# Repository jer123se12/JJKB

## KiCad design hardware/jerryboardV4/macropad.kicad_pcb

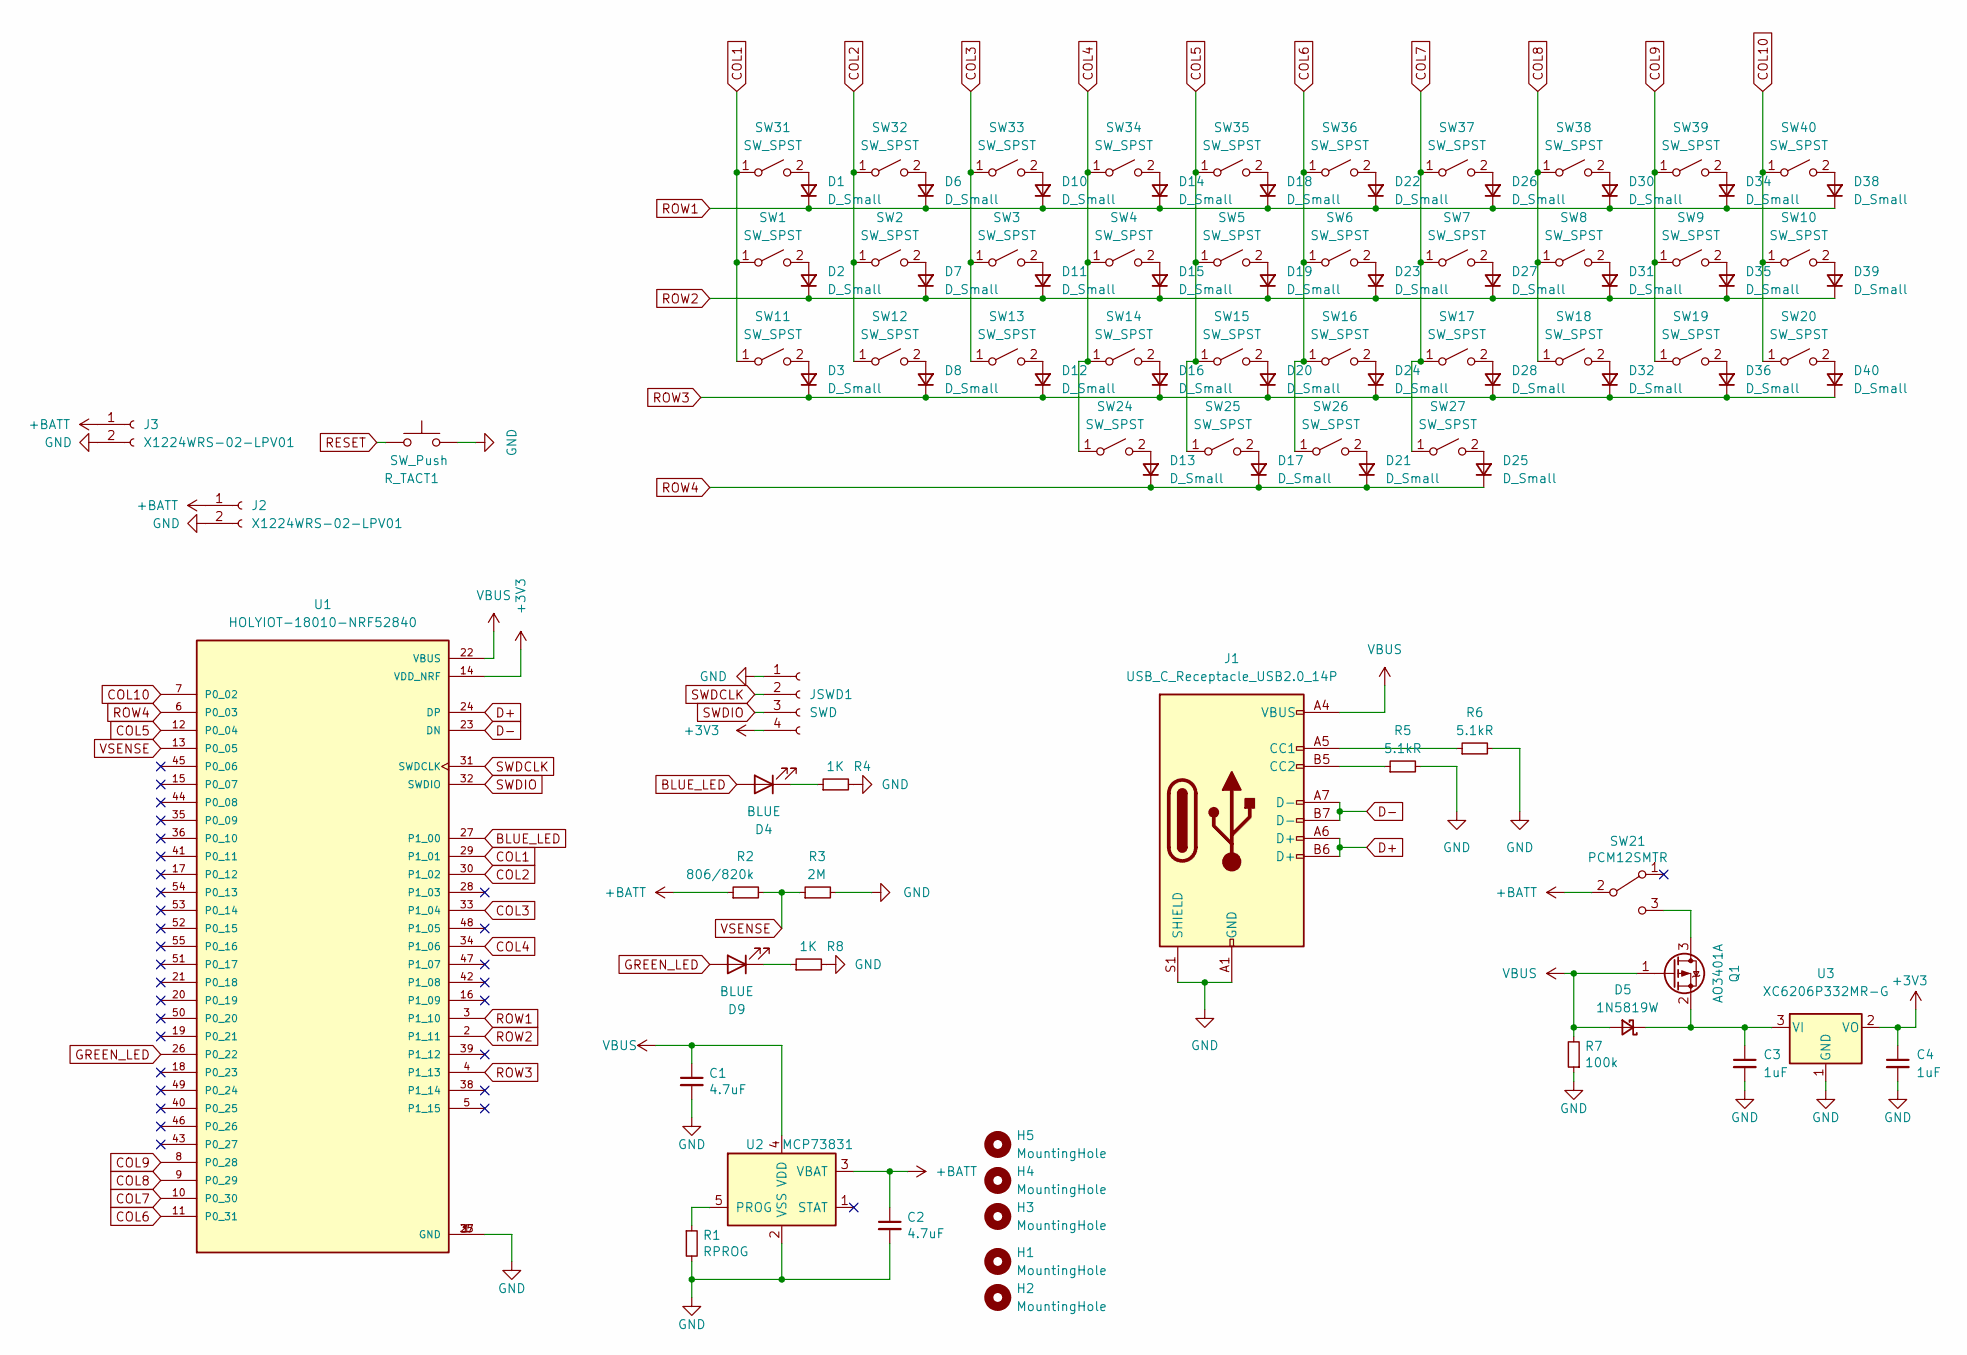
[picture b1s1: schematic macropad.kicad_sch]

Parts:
C1, C2: 4.7uF; C_0603_1608Metric; LCSC C19666
C3, C4: 1uF; C_0603_1608Metric; LCSC C1592
D1, D2, D3, D6, D7, D8, D10, D11, D12, D13, D14, D15, D16, D17, D18, D19, D20, D21, D22, D23, D24, D25, D26, D27, D28, D30, D31, D32, D34, D35, D36, D38, D39, D40: D_Small; D_SOD-123
D4, D9: BLUE; LED_0603_1608Metric; LCSC C72041
D5: 1N5819W; D_SOD-123; LCSC C169540
H1, H2, H3, H4, H5: MountingHole; MountingHole_5.3mm_M5
J1: USB_C_Receptacle_USB2.0_14P; USB_C_Receptacle_HRO_TYPE-C-31-M-12
J2: X1224WRS-02-LPV01; PinHeader_1x02_P2.54mm_Vertical; LCSC C528028
J3: X1224WRS-02-LPV01; Molex_Pico-EZmate_78171-0002_1x02-1MP_P1.20mm_Vertical; LCSC C528028
JSWD1: SWD; PinHeader_1x04_P2.54mm_Vertical
Q1: AO3401A; SOT-23; LCSC C15127
R1: RPROG; R_0603_1608Metric; LCSC C22978
R2: 806/820k; R_0603_1608Metric; LCSC C103828
R3: 2M; R_0603_1608Metric; LCSC C22976
R4, R8: 1K; R_0603_1608Metric; LCSC C21190
R5, R6: 5.1kR; R_0603_1608Metric
R7: 100k; R_0603_1608Metric; LCSC C25803
R_TACT1: SW_Push; Panasonic_EVQPUL_EVQPUC; LCSC C79175
SW1, SW2, SW3, SW4, SW5, SW6, SW7, SW8, SW9, SW10, SW11, SW12, SW13, SW14, SW15, SW16, SW17, SW18, SW19, SW20, SW24, SW25, SW26, SW27, SW31, SW32, SW33, SW34, SW35, SW36, SW37, SW38, SW39, SW40: SW_SPST; SW_Kailh_Choc_V1
SW21: PCM12SMTR; SW_SPDT_PCM12; LCSC C221841
U1: HOLYIOT-18010-NRF52840; XCVR_HOLYIOT-18010-NRF52840
U2: MCP73831; SOT-23-5; LCSC C14879
U3: XC6206P332MR-G; SOT-23; LCSC C5446

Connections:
+3V3: C4.1, JSWD1.4, U1.14 (VDD_NRF), U3.2 (VO)
+BATT: C2.1, J2.1, J3.1, R2.1, SW21.2 (B), U2.3 (VBAT)
BLUE_LED: D4.2 (A), U1.27 (P1_00)
COL1: SW1.1 (A), SW11.1 (A), SW31.1 (A), U1.29 (P1_01)
COL2: SW2.1 (A), SW12.1 (A), SW32.1 (A), U1.30 (P1_02)
COL3: SW3.1 (A), SW13.1 (A), SW33.1 (A), U1.33 (P1_04)
COL4: SW4.1 (A), SW14.1 (A), SW24.1 (A), SW34.1 (A), U1.34 (P1_06)
COL5: SW5.1 (A), SW15.1 (A), SW25.1 (A), SW35.1 (A), U1.12 (P0_04)
COL6: SW6.1 (A), SW16.1 (A), SW26.1 (A), SW36.1 (A), U1.11 (P0_31)
COL7: SW7.1 (A), SW17.1 (A), SW27.1 (A), SW37.1 (A), U1.10 (P0_30)
COL8: SW8.1 (A), SW18.1 (A), SW38.1 (A), U1.9 (P0_29)
COL9: SW9.1 (A), SW19.1 (A), SW39.1 (A), U1.8 (P0_28)
COL10: SW10.1 (A), SW20.1 (A), SW40.1 (A), U1.7 (P0_02)
D+: J1.A6 (D+), J1.B6 (D+), U1.24 (DP)
D-: J1.A7 (D-), J1.B7 (D-), U1.23 (DN)
GND: C1.2, C2.2, C3.2, C4.2, J1.A1 (GND), J1.A12 (GND), J1.B1 (GND), J1.B12 (GND), J1.S1 (SHIELD), J2.2, J3.2, JSWD1.1, R1.2, R3.2, R4.2, R5.2, R6.2, R7.1, R8.2, R_TACT1.2, U1.1 (GND), U1.25 (GND), U1.37 (GND), U2.2 (VSS), U3.1 (GND)
GREEN_LED: D9.2 (A), U1.26 (P0_22)
unnamed: D1.2 (A), SW31.2 (B)
unnamed: D2.2 (A), SW1.2 (B)
unnamed: D3.2 (A), SW11.2 (B)
unnamed: D4.1 (K), R4.1
unnamed: C3.1, D5.1 (K), Q1.2 (S), U3.3 (VI)
unnamed: D6.2 (A), SW32.2 (B)
unnamed: D7.2 (A), SW2.2 (B)
unnamed: D8.2 (A), SW12.2 (B)
unnamed: D9.1 (K), R8.1
unnamed: D10.2 (A), SW33.2 (B)
unnamed: D11.2 (A), SW3.2 (B)
unnamed: D12.2 (A), SW13.2 (B)
unnamed: D13.2 (A), SW24.2 (B)
unnamed: D14.2 (A), SW34.2 (B)
unnamed: D15.2 (A), SW4.2 (B)
unnamed: D16.2 (A), SW14.2 (B)
unnamed: D17.2 (A), SW25.2 (B)
unnamed: D18.2 (A), SW35.2 (B)
unnamed: D19.2 (A), SW5.2 (B)
unnamed: D20.2 (A), SW15.2 (B)
unnamed: D21.2 (A), SW26.2 (B)
unnamed: D22.2 (A), SW36.2 (B)
unnamed: D23.2 (A), SW6.2 (B)
unnamed: D24.2 (A), SW16.2 (B)
unnamed: D25.2 (A), SW27.2 (B)
unnamed: D26.2 (A), SW37.2 (B)
unnamed: D27.2 (A), SW7.2 (B)
unnamed: D28.2 (A), SW17.2 (B)
unnamed: D30.2 (A), SW38.2 (B)
unnamed: D31.2 (A), SW8.2 (B)
unnamed: D32.2 (A), SW18.2 (B)
unnamed: D34.2 (A), SW39.2 (B)
unnamed: D35.2 (A), SW9.2 (B)
unnamed: D36.2 (A), SW19.2 (B)
unnamed: D38.2 (A), SW40.2 (B)
unnamed: D39.2 (A), SW10.2 (B)
unnamed: D40.2 (A), SW20.2 (B)
unnamed: J1.A5 (CC1), R6.1
unnamed: J1.B5 (CC2), R5.1
unnamed: Q1.3 (D), SW21.3 (C)
unnamed: R1.1, U2.5 (PROG)
RESET: R_TACT1.1
ROW1: D1.1 (K), D6.1 (K), D10.1 (K), D14.1 (K), D18.1 (K), D22.1 (K), D26.1 (K), D30.1 (K), D34.1 (K), D38.1 (K), U1.3 (P1_10)
ROW2: D2.1 (K), D7.1 (K), D11.1 (K), D15.1 (K), D19.1 (K), D23.1 (K), D27.1 (K), D31.1 (K), D35.1 (K), D39.1 (K), U1.2 (P1_11)
ROW3: D3.1 (K), D8.1 (K), D12.1 (K), D16.1 (K), D20.1 (K), D24.1 (K), D28.1 (K), D32.1 (K), D36.1 (K), D40.1 (K), U1.4 (P1_13)
ROW4: D13.1 (K), D17.1 (K), D21.1 (K), D25.1 (K), U1.6 (P0_03)
SWDCLK: JSWD1.2, U1.31 (SWDCLK)
SWDIO: JSWD1.3, U1.32 (SWDIO)
VBUS: C1.1, D5.2 (A), J1.A4 (VBUS), J1.A9 (VBUS), J1.B4 (VBUS), J1.B9 (VBUS), Q1.1 (G), R7.2, U1.22 (VBUS), U2.4 (VDD)
VSENSE: R2.2, R3.1, U1.13 (P0_05)

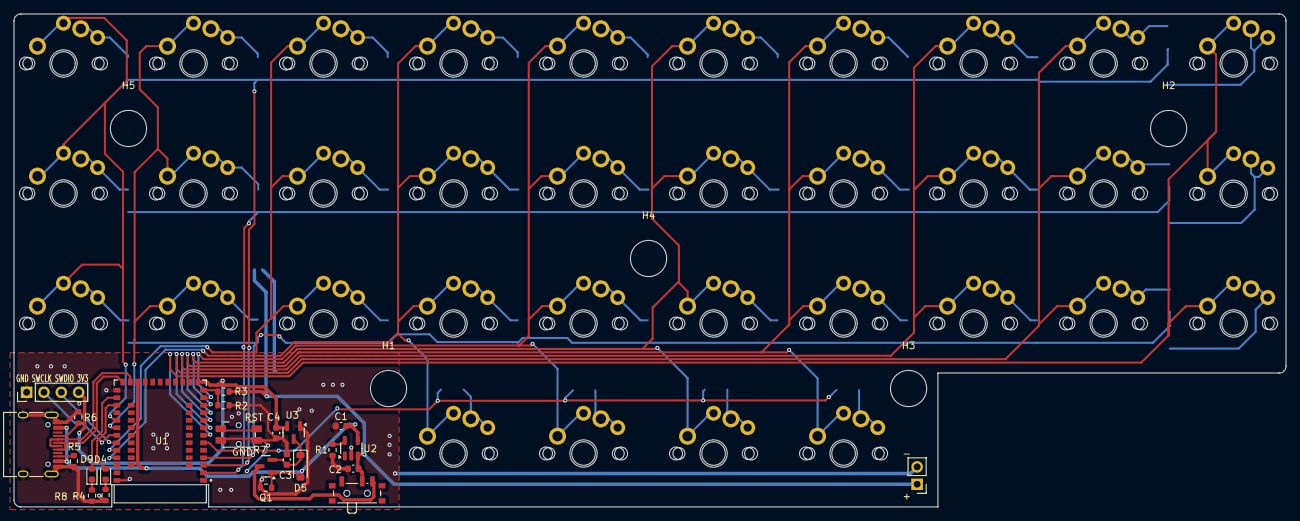
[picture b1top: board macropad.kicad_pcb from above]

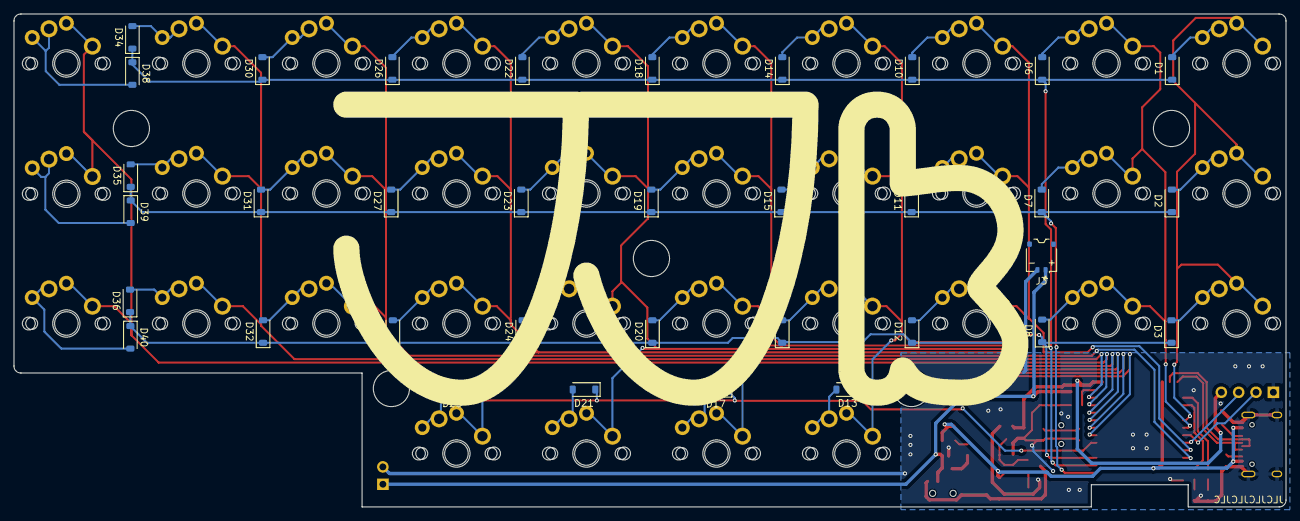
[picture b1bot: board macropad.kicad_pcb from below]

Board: 2 copper layers, 186.4 x 72.2 mm, 98 parts (35 on the bottom side), 66 nets.

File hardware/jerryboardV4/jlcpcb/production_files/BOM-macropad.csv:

Comment,Designator,Footprint,LCSC,Quantity
806/820k,R2,R_0603_1608Metric,C103828,1
BLUE,D9,LED_0603_1608Metric,C12624,1
MCP73831,U2,SOT-23-5,C14879,1
AO3401A,Q1,SOT-23,C15127,1
1uF,"C3,C4",C_0603_1608Metric,C1592,2
USB_C_Receptacle_USB2.0_14P,J1,USB_C_Receptacle_HRO_TYPE-C-31-M-12,C165948,1
1N5819W,D5,D_SOD-123,C169540,1
4.7uF,"C1,C2",C_0603_1608Metric,C19666,2
D_Small,"D1,D10,D11,D12,D13,D14,D15,D16,D17,D18,D19,D2,D20,D21,D22,D23,D24,D25,D26,D27,D28,D3,D30,D31,D32,D34,D35,D36,D38,D39,D40,D6,D7,D8",D_SOD-123,C2099,34
1K,"R4,R8",R_0603_1608Metric,C21190,2
PCM12SMTR,SW21,SW_SPDT_PCM12,C221841,1
BLUE,D4,LED_0603_1608Metric,C2288,1
2M,R3,R_0603_1608Metric,C22976,1
RPROG,R1,R_0603_1608Metric,C22978,1
100k,R7,R_0603_1608Metric,C25803,1
5.1kR,"R5,R6",R_0603_1608Metric,C269696,2
X1224WRS-02-LPV01,"J2,J3",PinHeader_1x02_P2.54mm_Vertical,C528028,2
XC6206P332MR-G,U3,SOT-23,C5446,1
SW_Push,R_TACT1,Panasonic_EVQPUL_EVQPUC,C79175,1
SWD,JSWD1,PinHeader_1x04_P2.54mm_Vertical,,1
SW_SPST,SW27,SW_Kailh_Choc_V1,,1
SW_SPST,SW20,SW_Kailh_Choc_V1,,1
SW_SPST,SW19,SW_Kailh_Choc_V1,,1
SW_SPST,SW33,SW_Kailh_Choc_V1,,1
SW_SPST,SW35,SW_Kailh_Choc_V1,,1
SW_SPST,SW12,SW_Kailh_Choc_V1,,1
SW_SPST,SW37,SW_Kailh_Choc_V1,,1
SW_SPST,SW26,SW_Kailh_Choc_V1,,1
SW_SPST,SW32,SW_Kailh_Choc_V1,,1
SW_SPST,SW15,SW_Kailh_Choc_V1,,1
SW_SPST,SW7,SW_Kailh_Choc_V1,,1
SW_SPST,SW34,SW_Kailh_Choc_V1,,1
SW_SPST,SW25,SW_Kailh_Choc_V1,,1
SW_SPST,SW38,SW_Kailh_Choc_V1,,1
SW_SPST,SW31,SW_Kailh_Choc_V1,,1
SW_SPST,SW13,SW_Kailh_Choc_V1,,1
SW_SPST,SW6,SW_Kailh_Choc_V1,,1
SW_SPST,SW2,SW_Kailh_Choc_V1,,1
SW_SPST,SW3,SW_Kailh_Choc_V1,,1
SW_SPST,SW11,SW_Kailh_Choc_V1,,1
SW_SPST,SW24,SW_Kailh_Choc_V1,,1
SW_SPST,SW1,SW_Kailh_Choc_V1,,1
SW_SPST,SW39,SW_Kailh_Choc_V1,,1
SW_SPST,SW4,SW_Kailh_Choc_V1,,1
SW_SPST,SW8,SW_Kailh_Choc_V1,,1
SW_SPST,SW5,SW_Kailh_Choc_V1,,1
SW_SPST,SW40,SW_Kailh_Choc_V1,,1
SW_SPST,SW10,SW_Kailh_Choc_V1,,1
SW_SPST,SW17,SW_Kailh_Choc_V1,,1
SW_SPST,SW16,SW_Kailh_Choc_V1,,1
SW_SPST,SW14,SW_Kailh_Choc_V1,,1
SW_SPST,SW18,SW_Kailh_Choc_V1,,1
SW_SPST,SW36,SW_Kailh_Choc_V1,,1
SW_SPST,SW9,SW_Kailh_Choc_V1,,1
HOLYIOT-18010-NRF52840,U1,XCVR_HOLYIOT-18010-NRF52840,,1

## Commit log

2025-10-21 removed extra stuff
